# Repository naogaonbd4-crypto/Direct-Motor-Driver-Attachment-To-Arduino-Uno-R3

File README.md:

# Direct-Motor-Driver-Attachment-To-Arduino-Uno-R3
exactly what the name says; meant to be compact. I made this for Science Olympiads Division C Electric Vehicle, where i needed a motor driver for my microcontroller (This pcb is not allowed to be used by OTHERS for the purpose of Science Olympiads according to rule 3C and rule 3KIII) If buying from PCBWAY, you can request for them to assemble it for you, but if not, a 10uf, .1uf, and a 2.2uf capacitor will be needed, as well as a drv8833PWP chip, a led, and sockets and pins.
It allows a max of 2 motors, and has pins 5,6,9,10 removed from the R3 to allow for the motors to be added. The power sources are connected as well

here is the schematic, i organized it into boards: 

The bottom connects to the Arduino Uno R3, while the top are the sockets to connect to R3 pins (except 5,6,9,10 which are already connected to the motors) and the OUT + EEP + ULT + VCC + GND pins of the motor driver

*also some terms relating to Half Life Hack Club YSWS
  I am currently collab with PCBWAY so they sponsor (and pay partially) for my projects, so I will not need funding from Hack Club

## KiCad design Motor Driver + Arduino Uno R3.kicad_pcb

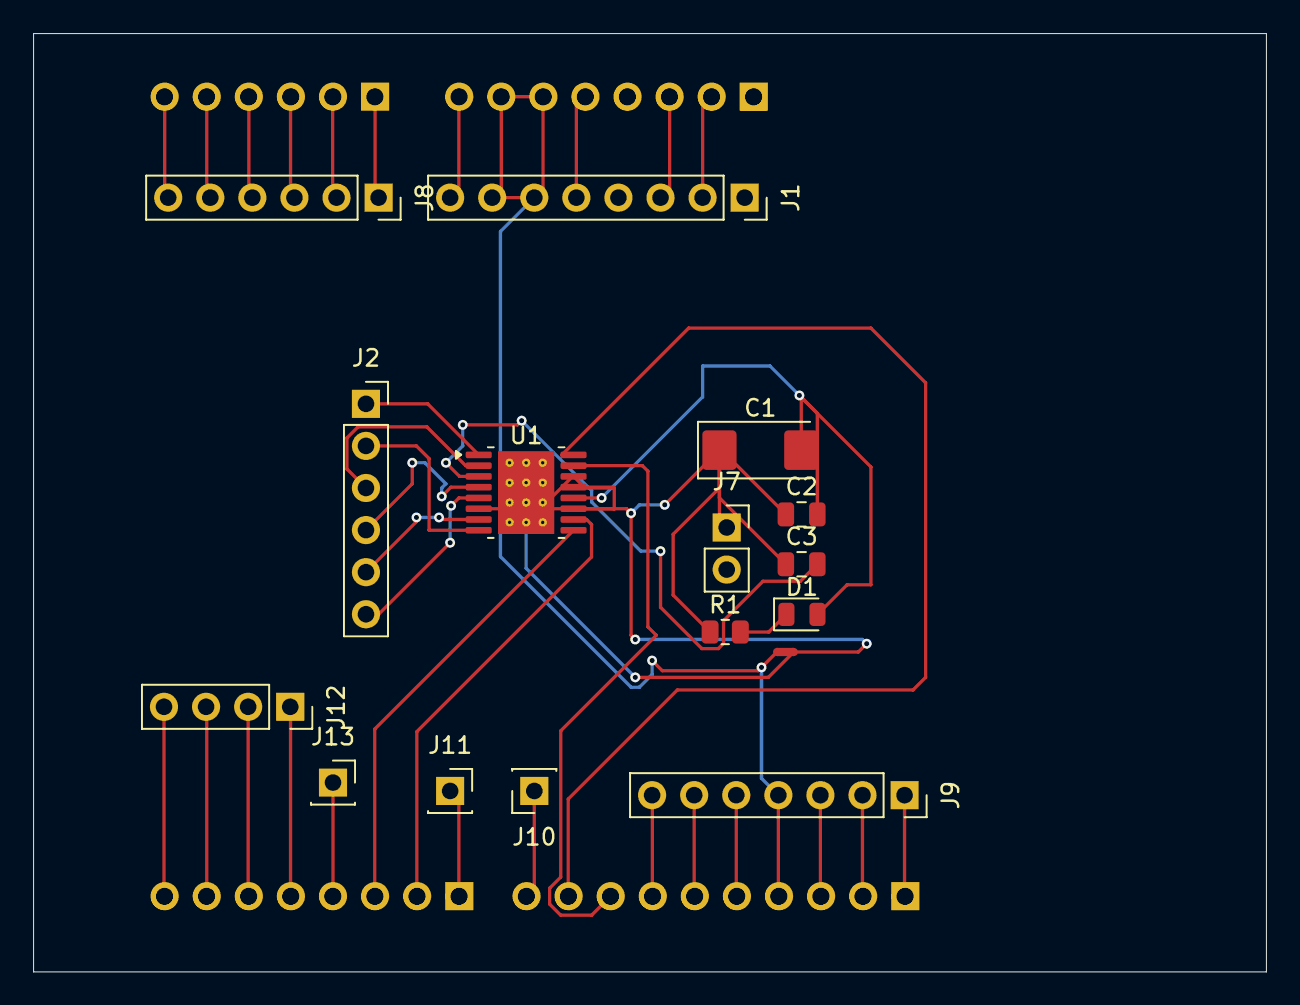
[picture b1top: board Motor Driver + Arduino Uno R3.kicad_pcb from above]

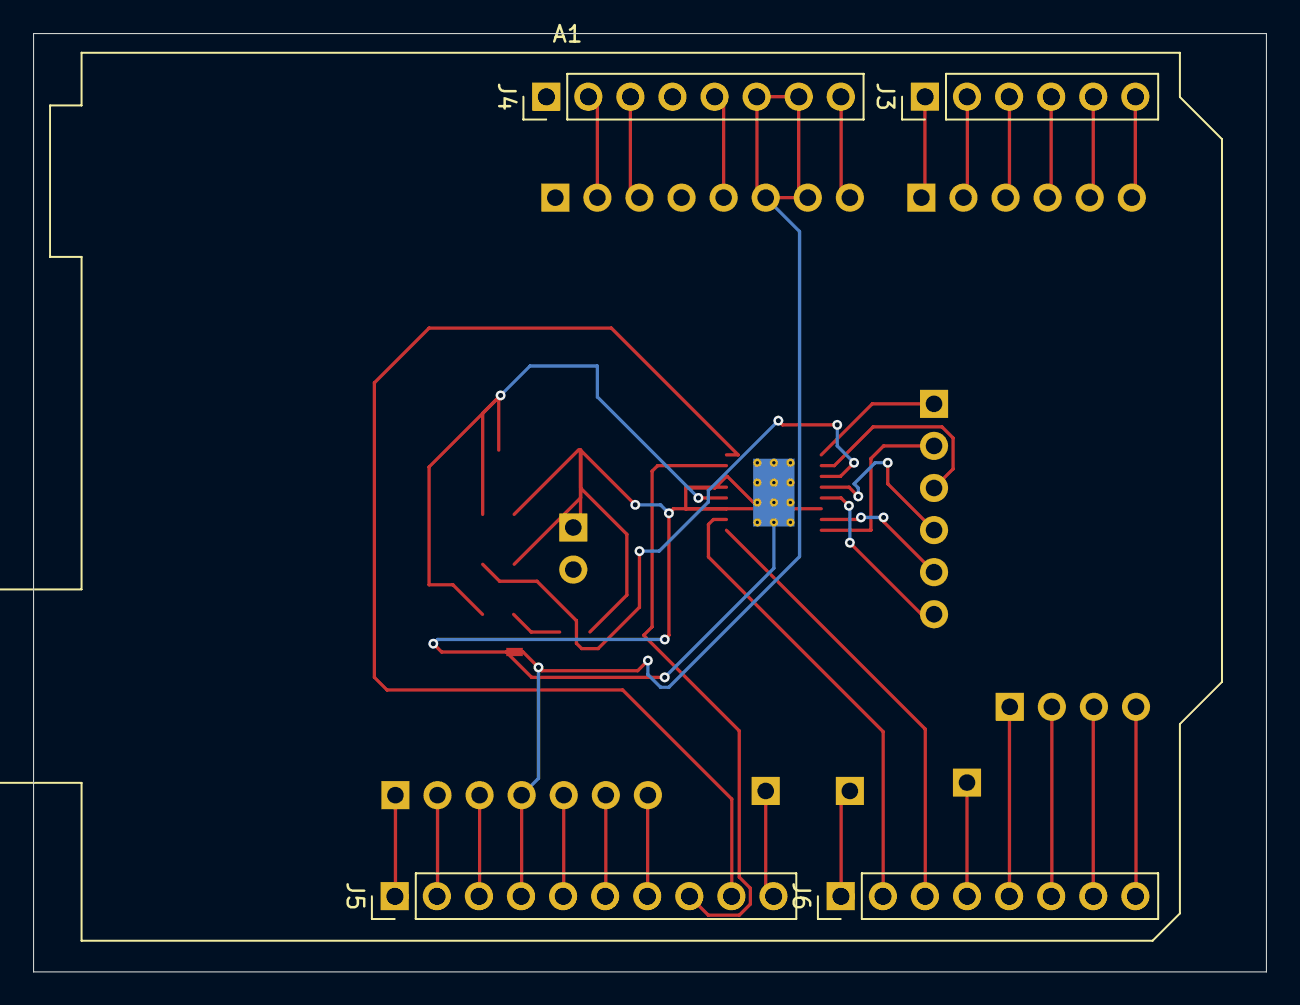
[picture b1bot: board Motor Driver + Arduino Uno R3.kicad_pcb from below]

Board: 2 copper layers, 74.4 x 56.6 mm, 21 parts (5 on the bottom side), 39 nets.

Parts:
A1: Arduino_UNO_R3
C1: 10 uF; CP_EIA-6032-20_AVX-F
C2: 0.1 uF; C_0805_2012Metric
C3: 2.2 uF; C_0805_2012Metric
D1: LED; LED_0805_2012Metric
J1: Conn_01x08_Socket; PinSocket_1x08_P2.54mm_Vertical
J2: Output DRV8833; PinSocket_1x06_P2.54mm_Vertical
J3: Conn_01x06_Pin; PinHeader_1x06_P2.54mm_Vertical
J4, J6: Conn_01x08_Pin; PinHeader_1x08_P2.54mm_Vertical
J5: Conn_01x10_Pin; PinHeader_1x10_P2.54mm_Vertical
J7: VCC and GND; PinSocket_1x02_P2.54mm_Vertical
J8: Conn_01x06_Socket; PinSocket_1x06_P2.54mm_Vertical
J9: Conn_01x07_Socket; PinSocket_1x07_P2.54mm_Vertical
J10, J11, J13: Conn_01x01_Socket; PinSocket_1x01_P2.54mm_Vertical
J12: Conn_01x04_Socket; PinSocket_1x04_P2.54mm_Vertical
NT1: NetTie_2; NetTie-2_SMD_Pad0.5mm
R1: 4.7K; R_0805_2012Metric
U1: DRV8833PWP; HTSSOP-16-1EP_4.4x5mm_P0.65mm_EP3.4x5mm_Mask2.46x2.31mm_The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

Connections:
+3V3: A1.4 (3V3), J4.4
+5V: A1.5 (+5V), J1.5, J4.5
+12V: A1.8 (VIN), J1.8, J4.8
A0: A1.9 (A0), J3.1, J8.1
A1: A1.10 (A1), J3.2, J8.2
A2: A1.11 (A2), J3.3, J8.3
A3: A1.12 (A3), J3.4, J8.4
AIN1: A1.24 (D9), J5.9, U1.16 (AIN1)
AIN2: A1.25 (D10), J5.8, U1.15 (AIN2)
AISEN: C3.2, U1.3 (AISEN)
AOUT1: J2.3, U1.2 (AOUT1)
AOUT2: J2.4, U1.4 (AOUT2)
AREF: A1.30 (AREF), J5.3, J9.3
BIN1: A1.20 (D5), J6.3, U1.9 (BIN1)
BIN2: A1.21 (D6), J6.2, U1.10 (BIN2)
BISEN: C1.1, C2.1, C3.1, J7.1, NT1.2, R1.1, U1.6 (BISEN), U1.11 (VCP), U1.13 (GND), U1.14 (VINT), U1.17 (GND)
BOUT1: J2.5, U1.7 (BOUT1)
BOUT2: J2.6, U1.5 (BOUT2)
D0: A1.15 (D0/RX), J6.8, J12.4
D1: A1.16 (D1/TX), J6.7, J12.3
D2: A1.17 (D2), J6.6, J12.2
D3: A1.18 (D3), J6.5, J12.1
D4: A1.19 (D4), J6.4, J13.1 (Pin_1_1)
D7: A1.22 (D7), J6.1, J11.1 (Pin_1_1)
D8: A1.23 (D8), J5.10, J10.1 (Pin_1_1)
D11: A1.26 (D11), J5.7, J9.7
D12: A1.27 (D12), J5.6, J9.6
D13: A1.28 (D13), J5.5, J9.5
FAULT: J2.2, U1.8 (~FAULT)
GND: A1.6 (GND), A1.7 (GND), A1.29 (GND), J1.6, J1.7, J4.6, J4.7, J5.4, J9.4, NT1.1
IOREF: A1.2 (IOREF), J1.2, J4.2
unnamed: D1.1 (K), R1.2
RESET: A1.3 (~RESET), J1.3, J4.3
SCL1: A1.14 (SCL/A5), J3.6, J8.6
SCL2: A1.32 (SCL/A5), J5.1, J9.1
SDA1: A1.13 (SDA/A4), J3.5, J8.5
SDA2: A1.31 (SDA/A4), J5.2, J9.2
SLEEP: J2.1, U1.1 (~SLEEP)
VM: C1.2, C2.2, D1.2 (A), U1.12 (VM)
